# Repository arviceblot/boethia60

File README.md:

# boethia60

A low profile, hotswap keyboard inspired by the HHBK layout, powered by [rmk](https://github.com/haobogu/rmk) with the rp2040 MCU.

## Features

- Low profile, with compatility for Choc V1 and V2 switches
- Vial support for realtime keymap changes
- HHKB style layout with split spacebars
- ESD protection because winters here are dry AF

## Layout

## Possible Improvements

- [ ] Relocate the USB connector to the left side.
- [ ] Change the USB connector to a mid-mount version. Right now, the bottom plate needs a cutout to fit the connector.

## Notes

This keyboard was mainly created as a learning experience. Most likely improvements could be made to the trace routing and other aspects.

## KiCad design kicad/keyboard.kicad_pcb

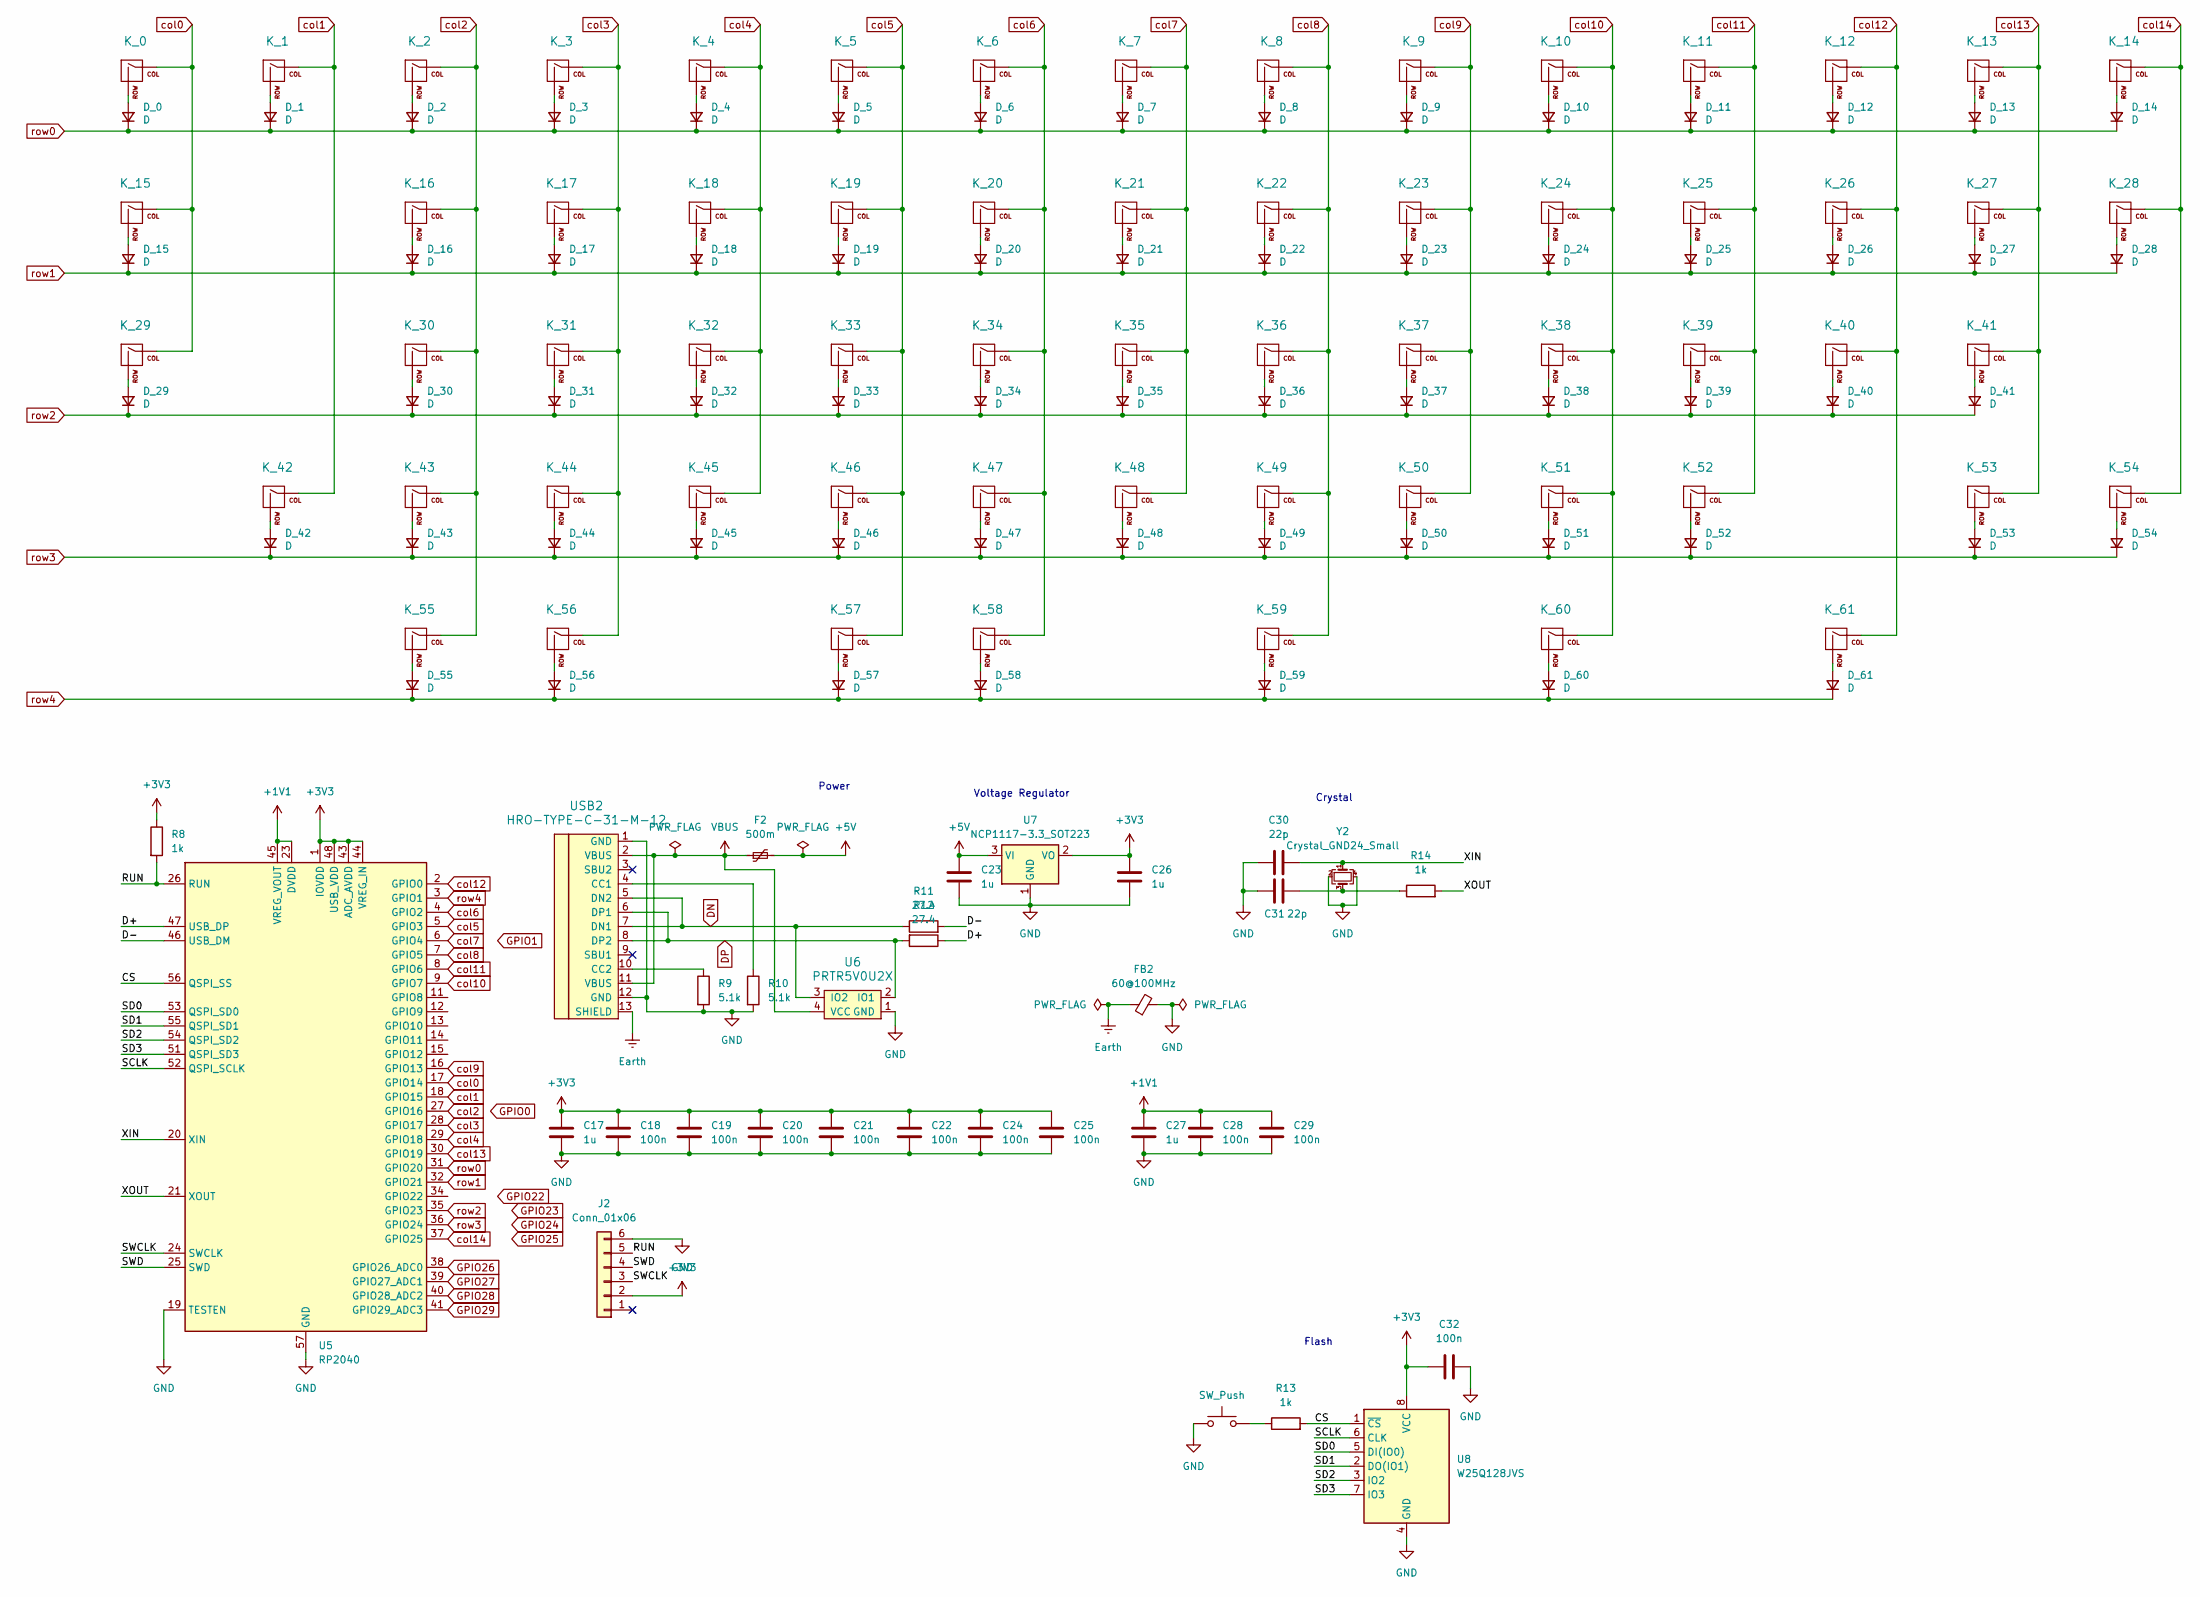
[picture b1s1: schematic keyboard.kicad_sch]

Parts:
C17, C23, C26, C27: 1u; C_0402_1005Metric; JLCPCB Part C52923
C18, C19, C20, C21, C22, C24, C25, C28, C29, C32: 100n; C_0402_1005Metric; JLCPCB Part C14663
C30, C31: 22p; C_0402_1005Metric; JLCPCB Part C1555
D_0, D_1, D_2, D_3, D_4, D_5, D_6, D_7, D_8, D_9, D_10, D_11, D_12, D_13, D_14, D_15, D_16, D_17, D_18, D_19, D_20, D_21, D_22, D_23, D_24, D_25, D_26, D_27, D_28, D_29, D_30, D_31, D_32, D_33, D_34, D_35, D_36, D_37, D_38, D_39, D_40, D_41, D_42, D_43, D_44, D_45, D_46, D_47, D_48, D_49, D_50, D_51, D_52, D_53, D_54, D_55, D_56, D_57, D_58, D_59, D_60, D_61: D; D_SOD-323
F2: 500m; Fuse_0805_2012Metric; JLCPCB Part C1015
FB2: 60@100MHz; L_0603_1608Metric; JLCPCB Part C14709
J2: Conn_01x06; Reset_Pretty-Mask
K_0, K_1, K_2, K_3, K_4, K_5, K_6, K_7, K_8, K_9, K_10, K_11, K_12, K_13, K_14, K_15, K_16, K_17, K_18, K_19, K_20, K_21, K_22, K_23, K_24, K_25, K_26, K_27, K_28, K_29, K_30, K_31, K_32, K_33, K_34, K_35, K_36, K_37, K_38, K_39, K_40, K_41, K_42, K_43, K_44, K_45, K_46, K_47, K_48, K_49, K_50, K_51, K_52, K_53, K_54, K_55, K_56, K_57, K_58, K_59, K_60, K_61: KEYSW; SW_Hotswap_Kailh_Choc_V1V2
R8, R13, R14: 1k; R_0402_1005Metric; JLCPCB Part C11702
R9, R10: 5.1k; R_0402_1005Metric; JLCPCB Part C25905
R11, R12: 27.4; R_0402_1005Metric; JLCPCB Part C274349
SW2: SW_Push; SW_SPST_SKQG_WithStem; JLCPCB Part C318884
U5: RP2040; QFN-56-1EP_7x7mm_P0.4mm_EP3.2x3.2mm; JLCPCB Part C2040
U6: PRTR5V0U2X; SOT-143; JLCPCB Part C2827688
U7: NCP1117-3.3_SOT223; SOT-23-3; JLCPCB Part C5446
U8: W25Q128JVS; SOIC-8_5.23x5.23mm_P1.27mm; JLCPCB Part C82317
USB2: HRO-TYPE-C-31-M-12; HRO-TYPE-C-31-M-12-HandSoldering
Y2: Crystal_GND24_Small; Crystal_SMD_3225-4Pin_3.2x2.5mm; JLCPCB Part C9002

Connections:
+1V1: C27.1, C28.1, C29.1, U5.23 (DVDD), U5.45 (VREG_VOUT), U5.50 (DVDD)
+3V3: C17.1, C18.1, C19.1, C20.1, C21.1, C22.1, C24.1, C25.1, C26.1, C32.1, J2.2, R8.1, U5.1 (IOVDD), U5.10 (IOVDD), U5.22 (IOVDD), U5.33 (IOVDD), U5.42 (IOVDD), U5.43 (ADC_AVDD), U5.44 (VREG_IN), U5.48 (USB_VDD), U5.49 (IOVDD), U7.2 (VO), U8.8 (VCC)
+5V: C23.1, F2.2, U7.3 (VI)
/CS: R13.2, U5.56 (QSPI_SS), U8.1 (~CS)
/D+: R12.1, U5.47 (USB_DP)
/D-: R11.2, U5.46 (USB_DM)
/RUN: J2.5, R8.2, U5.26 (RUN)
/SCLK: U5.52 (QSPI_SCLK), U8.6 (CLK)
/SD0: U5.53 (QSPI_SD0), U8.5 (DI(IO0))
/SD1: U5.55 (QSPI_SD1), U8.2 (DO(IO1))
/SD2: U5.54 (QSPI_SD2), U8.3 (IO2)
/SD3: U5.51 (QSPI_SD3), U8.7 (IO3)
/SWCLK: J2.3, U5.24 (SWCLK)
/SWD: J2.4, U5.25 (SWD)
/XIN: C30.2, U5.20 (XIN), Y2.1
/XOUT: R14.2, U5.21 (XOUT)
DN: R11.1, U6.3 (IO2), USB2.5 (DN2), USB2.7 (DN1)
DP: R12.2, U6.2 (IO1), USB2.6 (DP1), USB2.8 (DP2)
Earth: FB2.1, USB2.13 (SHIELD)
GND: C17.2, C18.2, C19.2, C20.2, C21.2, C22.2, C23.2, C24.2, C25.2, C26.2, C27.2, C28.2, C29.2, C30.1, C31.1, C32.2, FB2.2, J2.6, R9.2, R10.2, SW2.1, U5.19 (TESTEN), U5.57 (GND), U6.1 (GND), U7.1 (GND), U8.4 (GND), USB2.1 (GND), USB2.12 (GND), Y2.2, Y2.4
GPIO26: U5.38 (GPIO26_ADC0)
GPIO27: U5.39 (GPIO27_ADC1)
GPIO28: U5.40 (GPIO28_ADC2)
GPIO29: U5.41 (GPIO29_ADC3)
unnamed: C31.2, R14.1, Y2.3
unnamed: D_0.2 (A), K_0.2 (ROW)
unnamed: D_1.2 (A), K_1.2 (ROW)
unnamed: D_2.2 (A), K_2.2 (ROW)
unnamed: D_3.2 (A), K_3.2 (ROW)
unnamed: D_4.2 (A), K_4.2 (ROW)
unnamed: D_5.2 (A), K_5.2 (ROW)
unnamed: D_6.2 (A), K_6.2 (ROW)
unnamed: D_7.2 (A), K_7.2 (ROW)
unnamed: D_8.2 (A), K_8.2 (ROW)
unnamed: D_9.2 (A), K_9.2 (ROW)
unnamed: D_10.2 (A), K_10.2 (ROW)
unnamed: D_11.2 (A), K_11.2 (ROW)
unnamed: D_12.2 (A), K_12.2 (ROW)
unnamed: D_13.2 (A), K_13.2 (ROW)
unnamed: D_14.2 (A), K_14.2 (ROW)
unnamed: D_15.2 (A), K_15.2 (ROW)
unnamed: D_16.2 (A), K_16.2 (ROW)
unnamed: D_17.2 (A), K_17.2 (ROW)
unnamed: D_18.2 (A), K_18.2 (ROW)
unnamed: D_19.2 (A), K_19.2 (ROW)
unnamed: D_20.2 (A), K_20.2 (ROW)
unnamed: D_21.2 (A), K_21.2 (ROW)
unnamed: D_22.2 (A), K_22.2 (ROW)
unnamed: D_23.2 (A), K_23.2 (ROW)
unnamed: D_24.2 (A), K_24.2 (ROW)
unnamed: D_25.2 (A), K_25.2 (ROW)
unnamed: D_26.2 (A), K_26.2 (ROW)
unnamed: D_27.2 (A), K_27.2 (ROW)
unnamed: D_28.2 (A), K_28.2 (ROW)
unnamed: D_29.2 (A), K_29.2 (ROW)
unnamed: D_30.2 (A), K_30.2 (ROW)
unnamed: D_31.2 (A), K_31.2 (ROW)
unnamed: D_32.2 (A), K_32.2 (ROW)
unnamed: D_33.2 (A), K_33.2 (ROW)
unnamed: D_34.2 (A), K_34.2 (ROW)
unnamed: D_35.2 (A), K_35.2 (ROW)
unnamed: D_36.2 (A), K_36.2 (ROW)
unnamed: D_37.2 (A), K_37.2 (ROW)
unnamed: D_38.2 (A), K_38.2 (ROW)
unnamed: D_39.2 (A), K_39.2 (ROW)
unnamed: D_40.2 (A), K_40.2 (ROW)
unnamed: D_41.2 (A), K_41.2 (ROW)
unnamed: D_42.2 (A), K_42.2 (ROW)
unnamed: D_43.2 (A), K_43.2 (ROW)
unnamed: D_44.2 (A), K_44.2 (ROW)
unnamed: D_45.2 (A), K_45.2 (ROW)
unnamed: D_46.2 (A), K_46.2 (ROW)
unnamed: D_47.2 (A), K_47.2 (ROW)
unnamed: D_48.2 (A), K_48.2 (ROW)
unnamed: D_49.2 (A), K_49.2 (ROW)
unnamed: D_50.2 (A), K_50.2 (ROW)
unnamed: D_51.2 (A), K_51.2 (ROW)
unnamed: D_52.2 (A), K_52.2 (ROW)
unnamed: D_53.2 (A), K_53.2 (ROW)
unnamed: D_54.2 (A), K_54.2 (ROW)
unnamed: D_55.2 (A), K_55.2 (ROW)
unnamed: D_56.2 (A), K_56.2 (ROW)
unnamed: D_57.2 (A), K_57.2 (ROW)
unnamed: D_58.2 (A), K_58.2 (ROW)
unnamed: D_59.2 (A), K_59.2 (ROW)
unnamed: D_60.2 (A), K_60.2 (ROW)
unnamed: D_61.2 (A), K_61.2 (ROW)
unnamed: R13.1, SW2.2
unnamed: R10.1, USB2.4 (CC1)
unnamed: R9.1, USB2.10 (CC2)
VBUS: F2.1, U6.4 (VCC), USB2.2 (VBUS), USB2.11 (VBUS)
col0: K_0.1 (COL), K_15.1 (COL), K_29.1 (COL), U5.17 (GPIO14)
col1: K_1.1 (COL), K_42.1 (COL), U5.18 (GPIO15)
col2: K_2.1 (COL), K_16.1 (COL), K_30.1 (COL), K_43.1 (COL), K_55.1 (COL), U5.27 (GPIO16)
col3: K_3.1 (COL), K_17.1 (COL), K_31.1 (COL), K_44.1 (COL), K_56.1 (COL), U5.28 (GPIO17)
col4: K_4.1 (COL), K_18.1 (COL), K_32.1 (COL), K_45.1 (COL), U5.29 (GPIO18)
col5: K_5.1 (COL), K_19.1 (COL), K_33.1 (COL), K_46.1 (COL), K_57.1 (COL), U5.5 (GPIO3)
col6: K_6.1 (COL), K_20.1 (COL), K_34.1 (COL), K_47.1 (COL), K_58.1 (COL), U5.4 (GPIO2)
col7: K_7.1 (COL), K_21.1 (COL), K_35.1 (COL), K_48.1 (COL), U5.6 (GPIO4)
col8: K_8.1 (COL), K_22.1 (COL), K_36.1 (COL), K_49.1 (COL), K_59.1 (COL), U5.7 (GPIO5)
col9: K_9.1 (COL), K_23.1 (COL), K_37.1 (COL), K_50.1 (COL), U5.16 (GPIO13)
col10: K_10.1 (COL), K_24.1 (COL), K_38.1 (COL), K_51.1 (COL), K_60.1 (COL), U5.9 (GPIO7)
col11: K_11.1 (COL), K_25.1 (COL), K_39.1 (COL), K_52.1 (COL), U5.8 (GPIO6)
col12: K_12.1 (COL), K_26.1 (COL), K_40.1 (COL), K_61.1 (COL), U5.2 (GPIO0)
col13: K_13.1 (COL), K_27.1 (COL), K_41.1 (COL), K_53.1 (COL), U5.30 (GPIO19)
col14: K_14.1 (COL), K_28.1 (COL), K_54.1 (COL), U5.37 (GPIO25)
row0: D_0.1 (K), D_1.1 (K), D_2.1 (K), D_3.1 (K), D_4.1 (K), D_5.1 (K), D_6.1 (K), D_7.1 (K), D_8.1 (K), D_9.1 (K), D_10.1 (K), D_11.1 (K), D_12.1 (K), D_13.1 (K), D_14.1 (K), U5.31 (GPIO20)
row1: D_15.1 (K), D_16.1 (K), D_17.1 (K), D_18.1 (K), D_19.1 (K), D_20.1 (K), D_21.1 (K), D_22.1 (K), D_23.1 (K), D_24.1 (K), D_25.1 (K), D_26.1 (K), D_27.1 (K), D_28.1 (K), U5.32 (GPIO21)
row2: D_29.1 (K), D_30.1 (K), D_31.1 (K), D_32.1 (K), D_33.1 (K), D_34.1 (K), D_35.1 (K), D_36.1 (K), D_37.1 (K), D_38.1 (K), D_39.1 (K), D_40.1 (K), D_41.1 (K), U5.35 (GPIO23)
row3: D_42.1 (K), D_43.1 (K), D_44.1 (K), D_45.1 (K), D_46.1 (K), D_47.1 (K), D_48.1 (K), D_49.1 (K), D_50.1 (K), D_51.1 (K), D_52.1 (K), D_53.1 (K), D_54.1 (K), U5.36 (GPIO24)
row4: D_55.1 (K), D_56.1 (K), D_57.1 (K), D_58.1 (K), D_59.1 (K), D_60.1 (K), D_61.1 (K), U5.3 (GPIO1)

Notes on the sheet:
Flash
Power
Crystal
Voltage Regulator

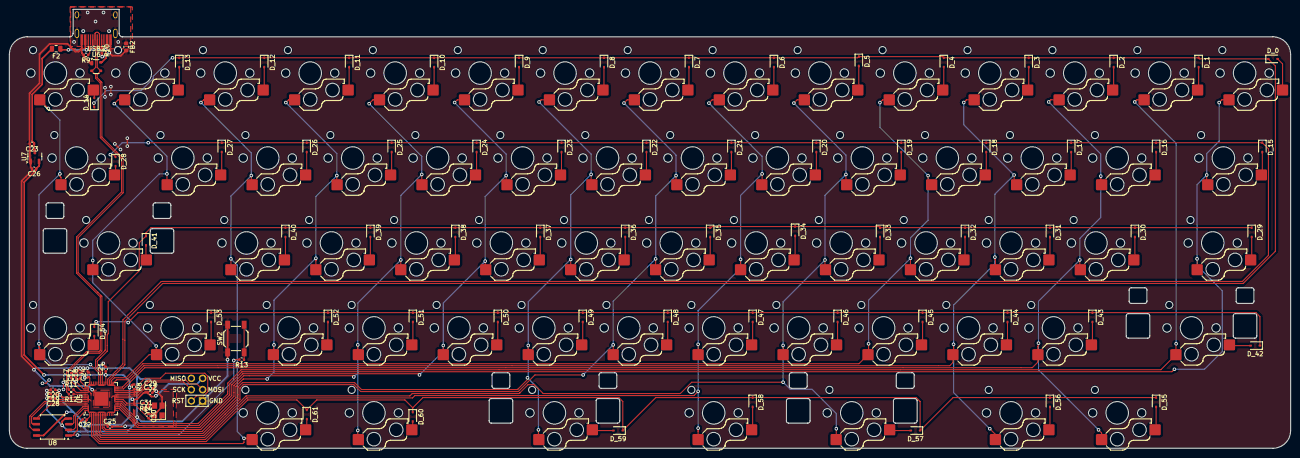
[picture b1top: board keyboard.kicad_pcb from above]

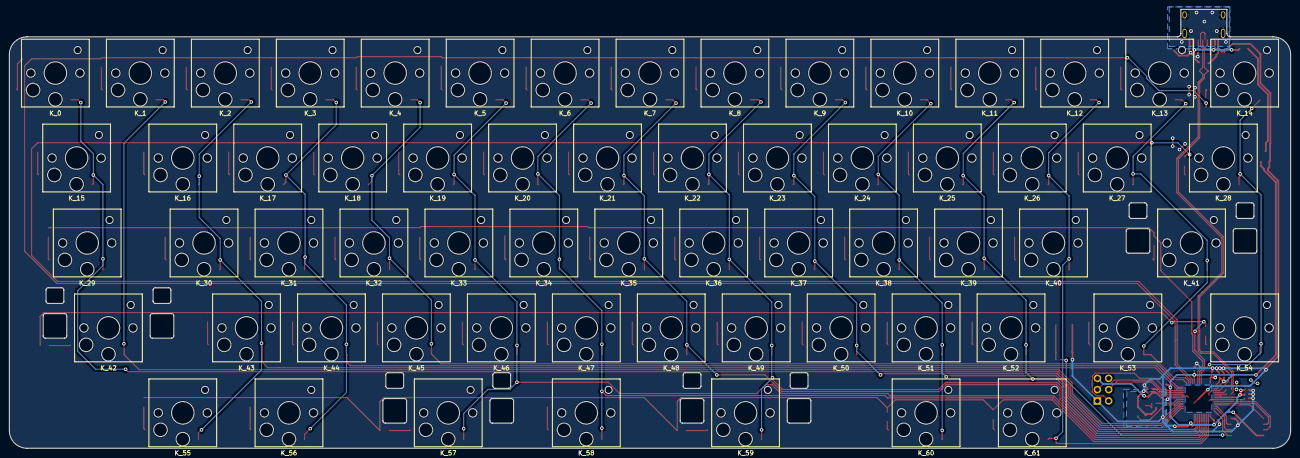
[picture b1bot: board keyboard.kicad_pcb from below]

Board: 2 copper layers, 287.3 x 98.4 mm, 157 parts (62 on the bottom side), 107 nets.

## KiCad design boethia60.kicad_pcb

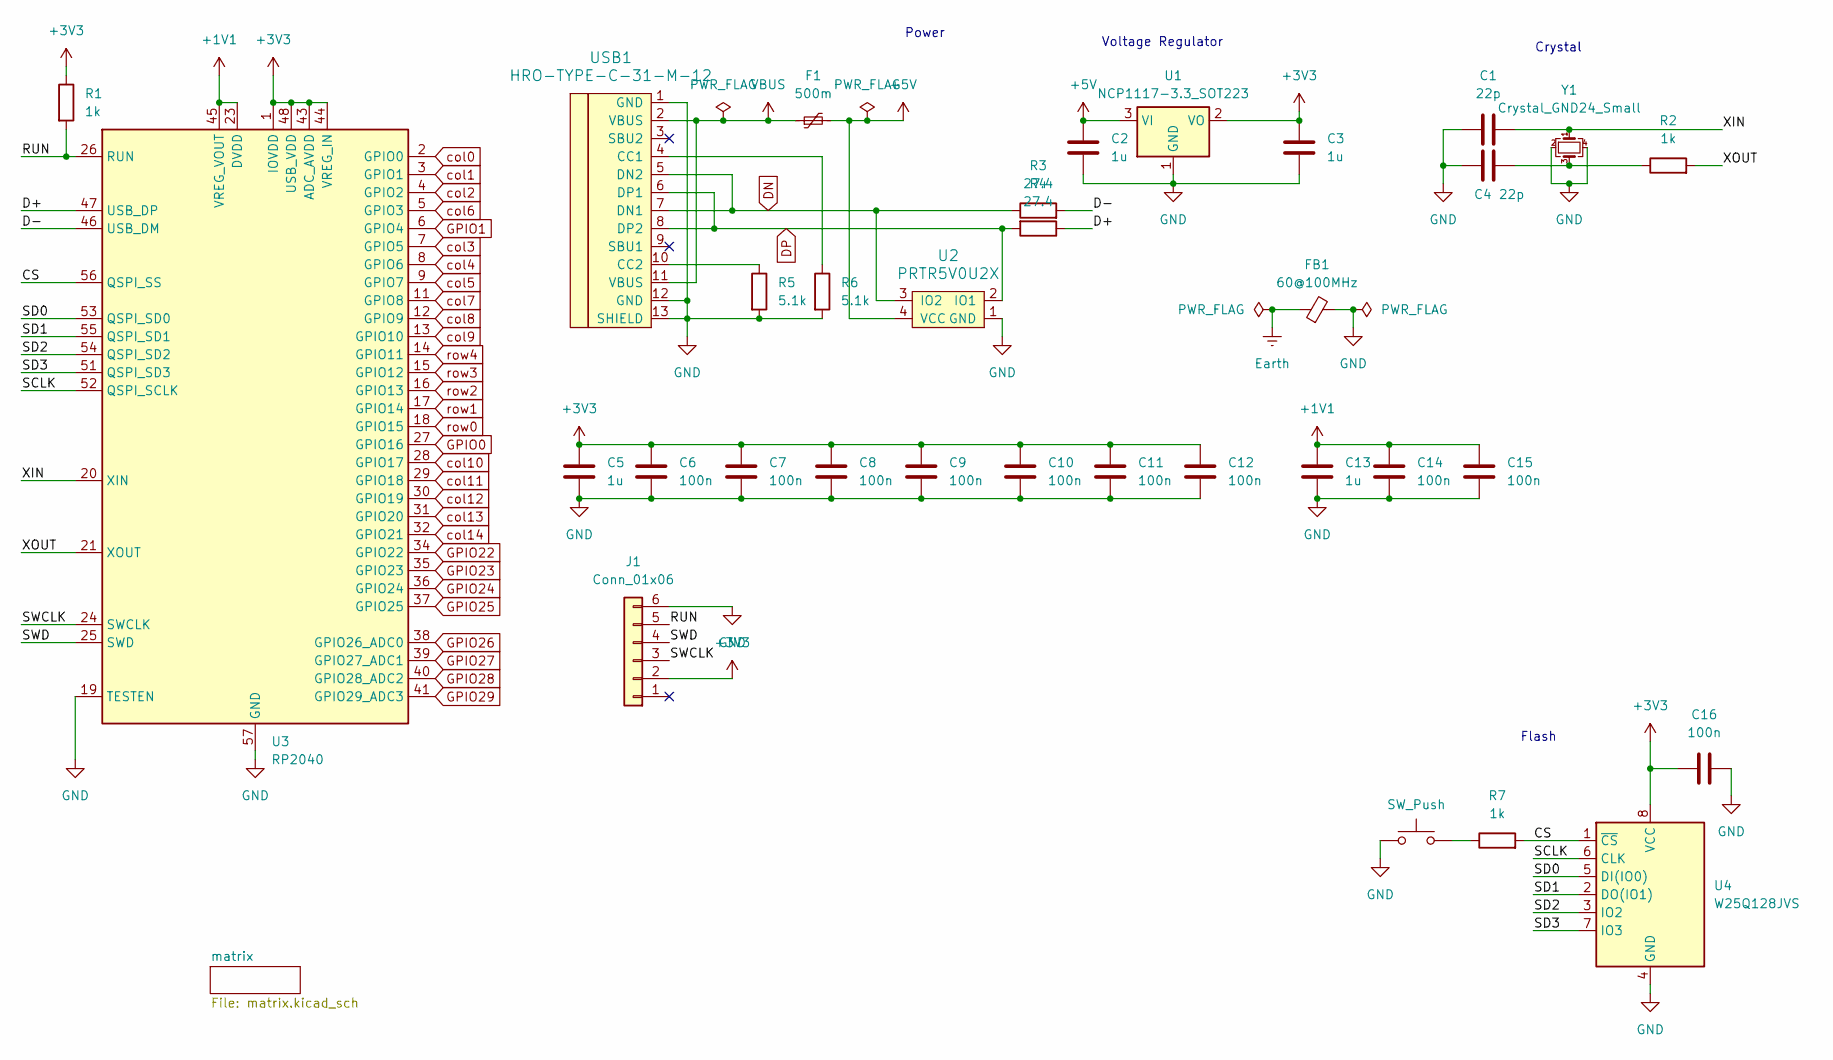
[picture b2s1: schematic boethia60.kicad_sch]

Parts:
C1, C4: 22p; C_0402_1005Metric; JLCPCB Part C1555
C2, C3, C5, C13: 1u; C_0402_1005Metric; JLCPCB Part C52923
C6, C7, C8, C9, C10, C11, C12, C14, C15, C16: 100n; C_0402_1005Metric; JLCPCB Part C14663
F1: 500m; Fuse_0805_2012Metric; JLCPCB Part C1015
FB1: 60@100MHz; L_0603_1608Metric; JLCPCB Part C14709
J1: Conn_01x06; Reset_Pretty-Mask
R1, R2, R7: 1k; R_0402_1005Metric; JLCPCB Part C11702
R3, R4: 27.4; R_0402_1005Metric; JLCPCB Part C274349
R5, R6: 5.1k; R_0402_1005Metric; JLCPCB Part C25905
SW1: SW_Push; SW_SPST_SKQG_WithStem; JLCPCB Part C318884
U1: NCP1117-3.3_SOT223; SOT-23-3; JLCPCB Part C5446
U2: PRTR5V0U2X; SOT-143; JLCPCB Part C2827688
U3: RP2040; QFN-56-1EP_7x7mm_P0.4mm_EP3.2x3.2mm; JLCPCB Part C2040
U4: W25Q128JVS; SOIC-8_5.23x5.23mm_P1.27mm; JLCPCB Part C82317
USB1: HRO-TYPE-C-31-M-12; HRO-TYPE-C-31-M-12-HandSoldering
Y1: Crystal_GND24_Small; Crystal_SMD_3225-4Pin_3.2x2.5mm; JLCPCB Part C9002

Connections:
+1V1: C13.1, C14.1, C15.1, U3.23 (DVDD), U3.45 (VREG_VOUT), U3.50 (DVDD)
+3V3: C3.1, C5.1, C6.1, C7.1, C8.1, C9.1, C10.1, C11.1, C12.1, C16.1, J1.2, R1.1, U1.2 (VO), U3.1 (IOVDD), U3.10 (IOVDD), U3.22 (IOVDD), U3.33 (IOVDD), U3.42 (IOVDD), U3.43 (ADC_AVDD), U3.44 (VREG_IN), U3.48 (USB_VDD), U3.49 (IOVDD), U4.8 (VCC)
+5V: C2.1, F1.2, U1.3 (VI), U2.4 (VCC)
/CS: R7.2, U3.56 (QSPI_SS), U4.1 (~CS)
/D+: R4.1, U3.47 (USB_DP)
/D-: R3.2, U3.46 (USB_DM)
/RUN: J1.5, R1.2, U3.26 (RUN)
/SCLK: U3.52 (QSPI_SCLK), U4.6 (CLK)
/SD0: U3.53 (QSPI_SD0), U4.5 (DI(IO0))
/SD1: U3.55 (QSPI_SD1), U4.2 (DO(IO1))
/SD2: U3.54 (QSPI_SD2), U4.3 (IO2)
/SD3: U3.51 (QSPI_SD3), U4.7 (IO3)
/SWCLK: J1.3, U3.24 (SWCLK)
/SWD: J1.4, U3.25 (SWD)
/XIN: C1.2, U3.20 (XIN), Y1.1
/XOUT: R2.2, U3.21 (XOUT)
DN: R3.1, U2.3 (IO2), USB1.5 (DN2), USB1.7 (DN1)
DP: R4.2, U2.2 (IO1), USB1.6 (DP1), USB1.8 (DP2)
Earth: FB1.1
GND: C1.1, C2.2, C3.2, C4.1, C5.2, C6.2, C7.2, C8.2, C9.2, C10.2, C11.2, C12.2, C13.2, C14.2, C15.2, C16.2, FB1.2, J1.6, R5.2, R6.2, SW1.1, U1.1 (GND), U2.1 (GND), U3.19 (TESTEN), U3.57 (GND), U4.4 (GND), USB1.1 (GND), USB1.12 (GND), USB1.13 (SHIELD), Y1.2, Y1.4
GPIO0: U3.27 (GPIO16)
GPIO1: U3.6 (GPIO4)
GPIO22: U3.34 (GPIO22)
GPIO23: U3.35 (GPIO23)
GPIO24: U3.36 (GPIO24)
GPIO25: U3.37 (GPIO25)
GPIO26: U3.38 (GPIO26_ADC0)
GPIO27: U3.39 (GPIO27_ADC1)
GPIO28: U3.40 (GPIO28_ADC2)
GPIO29: U3.41 (GPIO29_ADC3)
unnamed: C4.2, R2.1, Y1.3
unnamed: R7.1, SW1.2
unnamed: R6.1, USB1.4 (CC1)
unnamed: R5.1, USB1.10 (CC2)
VBUS: F1.1, USB1.2 (VBUS), USB1.11 (VBUS)
col0: U3.2 (GPIO0); also elsewhere on the board
col1: U3.3 (GPIO1); also elsewhere on the board
col2: U3.4 (GPIO2); also elsewhere on the board
col3: U3.7 (GPIO5); also elsewhere on the board
col4: U3.8 (GPIO6); also elsewhere on the board
col5: U3.9 (GPIO7); also elsewhere on the board
col6: U3.5 (GPIO3); also elsewhere on the board
col7: U3.11 (GPIO8); also elsewhere on the board
col8: U3.12 (GPIO9); also elsewhere on the board
col9: U3.13 (GPIO10); also elsewhere on the board
col10: U3.28 (GPIO17); also elsewhere on the board
col11: U3.29 (GPIO18); also elsewhere on the board
col12: U3.30 (GPIO19); also elsewhere on the board
col13: U3.31 (GPIO20); also elsewhere on the board
col14: U3.32 (GPIO21); also elsewhere on the board
row0: U3.18 (GPIO15); also elsewhere on the board
row1: U3.17 (GPIO14); also elsewhere on the board
row2: U3.16 (GPIO13); also elsewhere on the board
row3: U3.15 (GPIO12); also elsewhere on the board
row4: U3.14 (GPIO11); also elsewhere on the board

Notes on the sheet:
Voltage Regulator
Power
Crystal
Flash

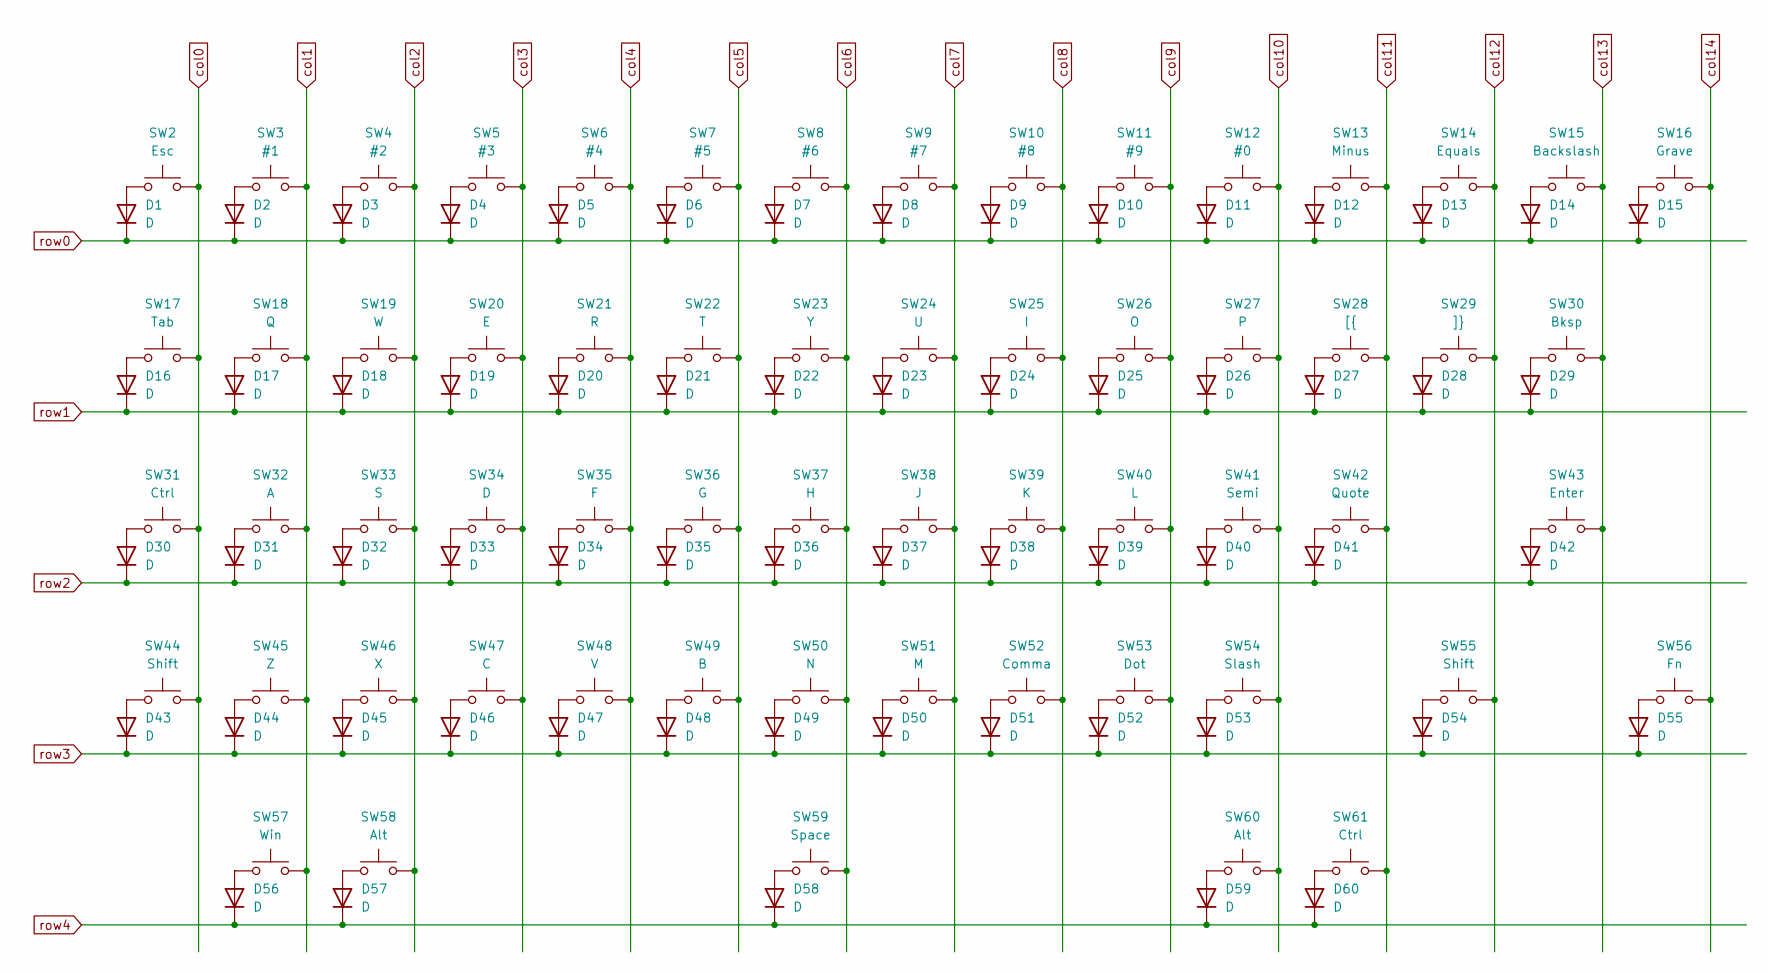
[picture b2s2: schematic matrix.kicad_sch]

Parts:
D1, D2, D3, D4, D5, D6, D7, D8, D9, D10, D11, D12, D13, D14, D15, D16, D17, D18, D19, D20, D21, D22, D23, D24, D25, D26, D27, D28, D29, D30, D31, D32, D33, D34, D35, D36, D37, D38, D39, D40, D41, D42, D43, D44, D45, D46, D47, D48, D49, D50, D51, D52, D53, D54, D55, D56, D57, D58, D59, D60: D; D_SOD-323; JLCPCB Part C2128
SW2: Esc; SW_choc_v2_HS_CPG135001S30_1u
SW3: #1; SW_choc_v2_HS_CPG135001S30_1u
SW4: #2; SW_choc_v2_HS_CPG135001S30_1u
SW5: #3; SW_choc_v2_HS_CPG135001S30_1u
SW6: #4; SW_choc_v2_HS_CPG135001S30_1u
SW7: #5; SW_choc_v2_HS_CPG135001S30_1u
SW8: #6; SW_choc_v2_HS_CPG135001S30_1u
SW9: #7; SW_choc_v2_HS_CPG135001S30_1u
SW10: #8; SW_choc_v2_HS_CPG135001S30_1u
SW11: #9; SW_choc_v2_HS_CPG135001S30_1u
SW12: #0; SW_choc_v2_HS_CPG135001S30_1u
SW13: Minus; SW_choc_v2_HS_CPG135001S30_1u
SW14: Equals; SW_choc_v2_HS_CPG135001S30_1u
SW15: Backslash; SW_choc_v2_HS_CPG135001S30_1u
SW16: Grave; SW_choc_v2_HS_CPG135001S30_1u
SW17: Tab; SW_choc_v2_HS_CPG135001S30_1.5u
SW18: Q; SW_choc_v2_HS_CPG135001S30_1u
SW19: W; SW_choc_v2_HS_CPG135001S30_1u
SW20: E; SW_choc_v2_HS_CPG135001S30_1u
SW21: R; SW_choc_v2_HS_CPG135001S30_1u
SW22: T; SW_choc_v2_HS_CPG135001S30_1u
SW23: Y; SW_choc_v2_HS_CPG135001S30_1u
SW24: U; SW_choc_v2_HS_CPG135001S30_1u
SW25: I; SW_choc_v2_HS_CPG135001S30_1u
SW26: O; SW_choc_v2_HS_CPG135001S30_1u
SW27: P; SW_choc_v2_HS_CPG135001S30_1u
SW28: [{; SW_choc_v2_HS_CPG135001S30_1u
SW29: ]}; SW_choc_v2_HS_CPG135001S30_1u
SW30: Bksp; SW_choc_v2_HS_CPG135001S30_1.5u
SW31: Ctrl; SW_choc_v2_HS_CPG135001S30_1.75u
SW32: A; SW_choc_v2_HS_CPG135001S30_1u
SW33: S; SW_choc_v2_HS_CPG135001S30_1u
SW34: D; SW_choc_v2_HS_CPG135001S30_1u
SW35: F; SW_choc_v2_HS_CPG135001S30_1u
SW36: G; SW_choc_v2_HS_CPG135001S30_1u
SW37: H; SW_choc_v2_HS_CPG135001S30_1u
SW38: J; SW_choc_v2_HS_CPG135001S30_1u
SW39: K; SW_choc_v2_HS_CPG135001S30_1u
SW40: L; SW_choc_v2_HS_CPG135001S30_1u
SW41: Semi; SW_choc_v2_HS_CPG135001S30_1u
SW42: Quote; SW_choc_v2_HS_CPG135001S30_1u
SW43: Enter; SW_choc_v2_HS_CPG135001S30_1u
SW44: Shift; SW_choc_v2_HS_CPG135001S30_1u
SW45: Z; SW_choc_v2_HS_CPG135001S30_1u
SW46: X; SW_choc_v2_HS_CPG135001S30_1u
SW47: C; SW_choc_v2_HS_CPG135001S30_1u
SW48: V; SW_choc_v2_HS_CPG135001S30_1u
SW49: B; SW_choc_v2_HS_CPG135001S30_1u
SW50: N; SW_choc_v2_HS_CPG135001S30_1u
SW51: M; SW_choc_v2_HS_CPG135001S30_1u
SW52: Comma; SW_choc_v2_HS_CPG135001S30_1u
SW53: Dot; SW_choc_v2_HS_CPG135001S30_1u
SW54: Slash; SW_choc_v2_HS_CPG135001S30_1u
SW55: Shift; SW_choc_v2_HS_CPG135001S30_1.75u
SW56: Fn; SW_choc_v2_HS_CPG135001S30_1u
SW57: Win; SW_choc_v2_HS_CPG135001S30_1u
SW58, SW60: Alt; SW_choc_v2_HS_CPG135001S30_1.5u
SW59: Space; SW_choc_v2_HS_CPG135001S30_1u
SW61: Ctrl; SW_choc_v2_HS_CPG135001S30_1u

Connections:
unnamed: D1.2 (A), SW2.1
unnamed: D2.2 (A), SW3.1
unnamed: D3.2 (A), SW4.1
unnamed: D4.2 (A), SW5.1
unnamed: D5.2 (A), SW6.1
unnamed: D6.2 (A), SW7.1
unnamed: D7.2 (A), SW8.1
unnamed: D8.2 (A), SW9.1
unnamed: D9.2 (A), SW10.1
unnamed: D10.2 (A), SW11.1
unnamed: D11.2 (A), SW12.1
unnamed: D12.2 (A), SW13.1
unnamed: D13.2 (A), SW14.1
unnamed: D14.2 (A), SW15.1
unnamed: D15.2 (A), SW16.1
unnamed: D16.2 (A), SW17.1
unnamed: D17.2 (A), SW18.1
unnamed: D18.2 (A), SW19.1
unnamed: D19.2 (A), SW20.1
unnamed: D20.2 (A), SW21.1
unnamed: D21.2 (A), SW22.1
unnamed: D22.2 (A), SW23.1
unnamed: D23.2 (A), SW24.1
unnamed: D24.2 (A), SW25.1
unnamed: D25.2 (A), SW26.1
unnamed: D26.2 (A), SW27.1
unnamed: D27.2 (A), SW28.1
unnamed: D28.2 (A), SW29.1
unnamed: D29.2 (A), SW30.1
unnamed: D30.2 (A), SW31.1
unnamed: D31.2 (A), SW32.1
unnamed: D32.2 (A), SW33.1
unnamed: D33.2 (A), SW34.1
unnamed: D34.2 (A), SW35.1
unnamed: D35.2 (A), SW36.1
unnamed: D36.2 (A), SW37.1
unnamed: D37.2 (A), SW38.1
unnamed: D38.2 (A), SW39.1
unnamed: D39.2 (A), SW40.1
unnamed: D40.2 (A), SW41.1
unnamed: D41.2 (A), SW42.1
unnamed: D42.2 (A), SW43.1
unnamed: D43.2 (A), SW44.1
unnamed: D44.2 (A), SW45.1
unnamed: D45.2 (A), SW46.1
unnamed: D46.2 (A), SW47.1
unnamed: D47.2 (A), SW48.1
unnamed: D48.2 (A), SW49.1
unnamed: D49.2 (A), SW50.1
unnamed: D50.2 (A), SW51.1
unnamed: D51.2 (A), SW52.1
unnamed: D52.2 (A), SW53.1
unnamed: D53.2 (A), SW54.1
unnamed: D54.2 (A), SW55.1
unnamed: D55.2 (A), SW56.1
unnamed: D56.2 (A), SW57.1
unnamed: D57.2 (A), SW58.1
unnamed: D58.2 (A), SW59.1
unnamed: D59.2 (A), SW60.1
unnamed: D60.2 (A), SW61.1
col0: SW2.2, SW17.2, SW31.2, SW44.2; also elsewhere on the board
col1: SW3.2, SW18.2, SW32.2, SW45.2, SW57.2; also elsewhere on the board
col2: SW4.2, SW19.2, SW33.2, SW46.2, SW58.2; also elsewhere on the board
col3: SW5.2, SW20.2, SW34.2, SW47.2; also elsewhere on the board
col4: SW6.2, SW21.2, SW35.2, SW48.2; also elsewhere on the board
col5: SW7.2, SW22.2, SW36.2, SW49.2; also elsewhere on the board
col6: SW8.2, SW23.2, SW37.2, SW50.2, SW59.2; also elsewhere on the board
col7: SW9.2, SW24.2, SW38.2, SW51.2; also elsewhere on the board
col8: SW10.2, SW25.2, SW39.2, SW52.2; also elsewhere on the board
col9: SW11.2, SW26.2, SW40.2, SW53.2; also elsewhere on the board
col10: SW12.2, SW27.2, SW41.2, SW54.2, SW60.2; also elsewhere on the board
col11: SW13.2, SW28.2, SW42.2, SW61.2; also elsewhere on the board
col12: SW14.2, SW29.2, SW55.2; also elsewhere on the board
col13: SW15.2, SW30.2, SW43.2; also elsewhere on the board
col14: SW16.2, SW56.2; also elsewhere on the board
row0: D1.1 (K), D2.1 (K), D3.1 (K), D4.1 (K), D5.1 (K), D6.1 (K), D7.1 (K), D8.1 (K), D9.1 (K), D10.1 (K), D11.1 (K), D12.1 (K), D13.1 (K), D14.1 (K), D15.1 (K); also elsewhere on the board
row1: D16.1 (K), D17.1 (K), D18.1 (K), D19.1 (K), D20.1 (K), D21.1 (K), D22.1 (K), D23.1 (K), D24.1 (K), D25.1 (K), D26.1 (K), D27.1 (K), D28.1 (K), D29.1 (K); also elsewhere on the board
row2: D30.1 (K), D31.1 (K), D32.1 (K), D33.1 (K), D34.1 (K), D35.1 (K), D36.1 (K), D37.1 (K), D38.1 (K), D39.1 (K), D40.1 (K), D41.1 (K), D42.1 (K); also elsewhere on the board
row3: D43.1 (K), D44.1 (K), D45.1 (K), D46.1 (K), D47.1 (K), D48.1 (K), D49.1 (K), D50.1 (K), D51.1 (K), D52.1 (K), D53.1 (K), D54.1 (K), D55.1 (K); also elsewhere on the board
row4: D56.1 (K), D57.1 (K), D58.1 (K), D59.1 (K), D60.1 (K); also elsewhere on the board

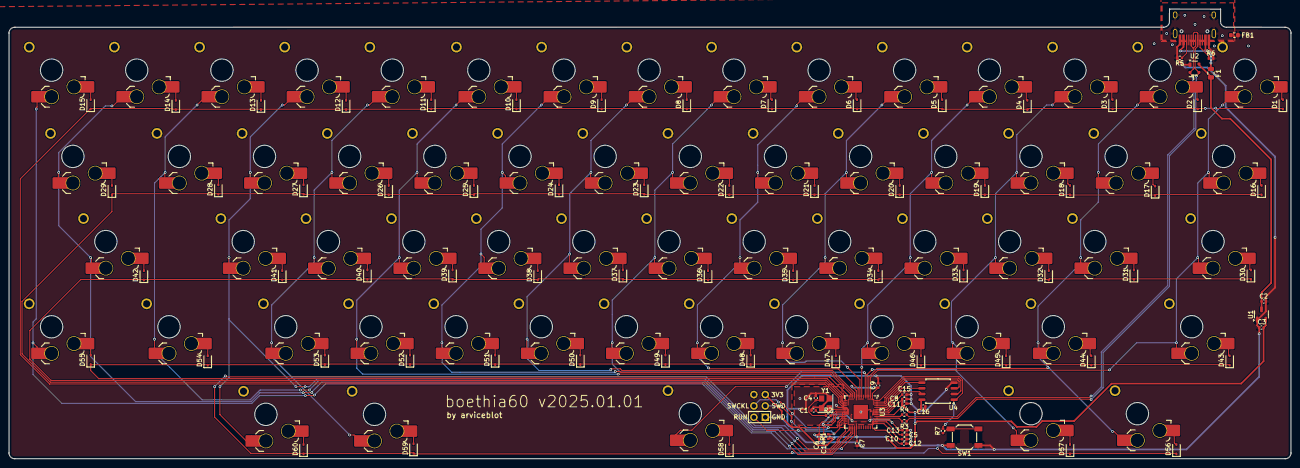
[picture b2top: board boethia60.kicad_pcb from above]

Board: 2 copper layers, 286.7 x 100.6 mm, 153 parts (0 on the bottom side), 104 nets.

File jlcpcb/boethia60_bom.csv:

"Reference","Value","Datasheet","Footprint","Qty","JLCPCB Part"
"C1,C4","22p","~","Capacitor_SMD:C_0402_1005Metric","2","C1555"
"C2,C3,C5,C13","1u","~","Capacitor_SMD:C_0402_1005Metric","4","C52923"
"C6,C7,C8,C9,C10,C11,C12,C14,C15,C16","100n","~","Capacitor_SMD:C_0402_1005Metric","10","C14663"
"D1,D2,D3,D4,D5,D6,D7,D8,D9,D10,D11,D12,D13,D14,D15,D16,D17,D18,D19,D20,D21,D22,D23,D24,D25,D26,D27,D28,D29,D30,D31,D32,D33,D34,D35,D36,D37,D38,D39,D40,D41,D42,D43,D44,D45,D46,D47,D48,D49,D50,D51,D52,D53,D54,D55,D56,D57,D58,D59,D60","D","~","Diode_SMD:D_SOD-323","60","C2128"
"F1","500m","~","Fuse_0805_2012Metric","1","C1015"
"FB1","60@100MHz","~","Inductor_SMD:L_0603_1608Metric","1","C14709"
"R1,R2,R7","1k","~","R_0402_1005Metric","3","C11702"
"R3,R4","27.4","~","R_0402_1005Metric","2","C274349"
"R5,R6","5.1k","~","R_0402_1005Metric","2","C25905"
"SW1","SW_Push","~","Button_Switch_SMD:SW_SPST_SKQG_WithStem","1","C318884"
"U1","NCP1117-3.3_SOT223","http://www.onsemi.com/pub_link/Collateral/NCP1117-D.PDF","Package_TO_SOT_SMD:SOT-23-3","1","C5446"
"U2","PRTR5V0U2X","","Package_TO_SOT_SMD:SOT-143","1","C2827688"
"U3","RP2040","https://datasheets.raspberrypi.com/rp2040/rp2040-datasheet.pdf","Package_DFN_QFN:QFN-56-1EP_7x7mm_P0.4mm_EP3.2x3.2mm","1","C2040"
"U4","W25Q128JVS","https://www.winbond.com/resource-files/w25q128jv_dtr%20revc%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","Package_SO:SOIC-8_5.23x5.23mm_P1.27mm","1","C82317"
"Y1","Crystal_GND24_Small","~","Crystal:Crystal_SMD_3225-4Pin_3.2x2.5mm","1","C9002"

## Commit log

2025-01-11 Initial import
2025-01-14 Everything is coming together.
2025-01-14 Fixed lonely column.
2025-01-14 Add initial rmk keymap, needs fixing.
2025-01-14 Change footprints, fix errors, WIP BOM.
2025-01-15 Fix firmware pins.
2025-01-16 Add another kicad project version.
2025-01-17 Complete routing and fill zones.
2025-01-17 Update.
2025-01-17 Add preview plate and case files.
2025-01-18 Update annotations.
2025-01-18 Update firmware for new schematic.
2025-01-18 Add top and bottom plates.
2025-01-19 Add KLE keymap and update Vial keymap.
2025-01-19 Add test readme.
2025-01-19 Fix layout image.
2025-01-20 Fix incorrect package BOM item.
2025-02-01 Add prototype image
2025-02-02 Document possible improvements.
